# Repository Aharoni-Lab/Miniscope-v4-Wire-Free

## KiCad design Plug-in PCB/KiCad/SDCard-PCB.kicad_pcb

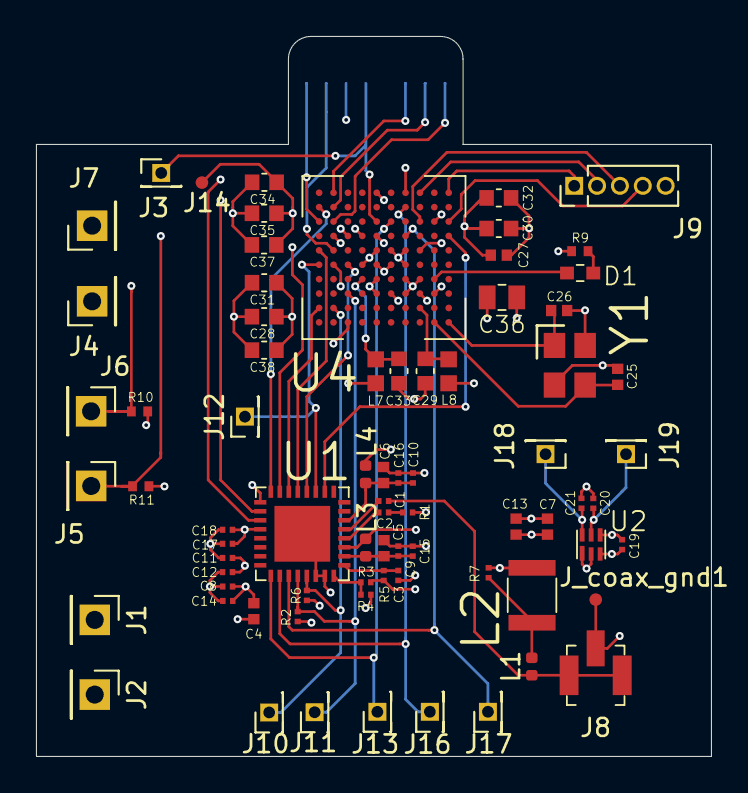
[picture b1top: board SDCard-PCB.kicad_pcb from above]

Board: 4 copper layers, 37.5 x 40.0 mm, 76 parts (1 on the bottom side), 47 nets.

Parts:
C1, C8, C9, C10, C11, C12: GRM033R61A104ME15D; C_0201_0603Metric_L
C2: GRM033R61C473KE84D; C_0201_0603Metric_L
C3, C19, C20, C21: GRM033R61A105ME15D; C_0201_0603Metric_L
C4, C5: GRM155R60J475ME47D; C_0402_1005Metric_L
C6: GRJ155R60J106ME11D; C_0402_1005Metric_L
C7, C13: GRM155R60J106ME15D; C_0402_1005Metric_L
C14, C15, C16, C17, C18: GRM033R71A103KA01D; C_0201_0603Metric_L
C25, C26: GRM1555C1H120JA01D; C_0402_1005Metric_L
C27: GRM155R60J475ME87D; C_0402_1005Metric_L
C28, C29, C30, C31, C32, C33, C34, C35, C37, C38: GCJ188R71E104KA12D; C_0603_1608Metric_L
C36: GCM21BR71E105KA56L; C_0805_2012Metric_L
D1: Vishay / Lite-On LTST-C191KRKT; LED_SC80X160X65L40L
J1, J2, J4, J5, J6, J7: Conn_01x01; PinHeader_1x01_P2.54mm_Vertical
J3, J10, J11, J12, J13, J16, J17, J18, J19: Conn_01x01; PinHeader_1x01_P1.27mm_Vertical
J8: Conn_Coaxial; U_FL-R-SMT_10_
J9: Conn_01x05; PinHeader_1x05_P1.27mm_Vertical
J14: Conn_01x01; Conn_1x1_700_Circular_Pad
J15: Conn_01x08; 1x8_microSD
J_coax_gnd1: Conn_01x01; Conn_1x1_700_Circular_Pad
L1, L3, L4: BLM15HD102SN1D; L_0402_1005Metric
L2: ADL3225V-470MT-TL000; L_1210_3225Metric_L
L7, L8: BLM18PG471SN1D; L_0603_1608Metric_L
R1: ERJ-1GEF49R9C; R_0201_0603Metric_ERJ_L
R2, R6: ERJ-1GEF3321C; R_0201_0603Metric_ERJ_L
R3, R5: ERJ-1GEF1002C; R_0201_0603Metric_ERJ_L
R4: ERJ-1GEF1003C; R_0201_0603Metric_ERJ_L
R7: MMBT3904LP-7B; R_0201_0603Metric_ERJ_L
R9: 499; R_0402_1005Metric_ERJ_L
R10, R11: 100k; R_0402_1005Metric_ERJ_L
U1: DS90UB933-Q1; QFN_33_P50_500X500X80L40X24T310L
U2: TLV7103318DSER; SON_6_P50_150X150X80L50X25L
U4: ATSAME70N21A-CN; BGA_100_CP80_10X10_900X900X110B40L
Y1: ABM8G-12.000MHZ-4Y-T3; OSCCC320X250X100L80X100

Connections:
+1V2: C34.1, C35.1, C36.1, C37.1, J14.1, L7.1, L8.2, U4.C3, U4.C6, U4.D6, U4.G6
+1V8: C4.1, C8.1, C11.1, C12.1, C14.1, C17.1, C18.1, C20.1, C27.1, C28.1, C30.1, C31.1, C32.1, C38.1, J2.1, J4.1, J19.1, L3.2, L4.2, R3.1, R5.1, R10.1, R11.1, U1.11, U1.25, U1.28, U2.5, U4.C2, U4.C5, U4.E5, U4.E6, U4.F3, U4.G7
+3V3: C21.1, J1.1, J18.1, R2.1, R6.1, U2.6
+5V: C7.1, C13.1, C19.1, L2.2, R7.1, U2.1, U2.2, U2.3
/Connectors/SWDCLK-Rec: J6.1, R10.2, U4.E9
/Connectors/SWDIO-Rec: J5.1, R11.2, U4.G8
/OnBoardMCU/FRAME_VALID: J16.1, U1.2, U4.J4
/OnBoardMCU/IMG_out0: J12.1, U1.19, U4.E10
/OnBoardMCU/IMG_out1: U1.20, U4.E8
/OnBoardMCU/IMG_out2: U1.21, U4.F10
/OnBoardMCU/IMG_out3: U1.22, U4.B10
/OnBoardMCU/IMG_out4: U1.23, U4.G9
/OnBoardMCU/IMG_out5: U1.24, U4.J10
/OnBoardMCU/IMG_out6: U1.26, U4.K6
/OnBoardMCU/IMG_out7: U1.27, U4.K4
/OnBoardMCU/LINE_VALID: J13.1, U1.1, U4.H5
/OnBoardMCU/PXL_CLK: J17.1, U1.3, U4.G4
/OnBoardMCU/RED_LED: D1.2, U4.D2
/OnBoardMCU/SCL: J11.1, R2.2, U1.4, U4.C8
/OnBoardMCU/SDA: J10.1, R6.2, U1.5, U4.B9
/OnBoardMCU/SER_CLK: U1.18, U4.G1
/OnBoardMCU/VDDPLL: C33.1, L7.2, U4.D7
/OnBoardMCU/VDDUTMIC: C29.1, L8.1, U4.B3
/OnBoardMCU/WXB_CLK: J3.1, J15.5, U4.H6
/OnBoardMCU/WXB_CMD: J15.3, U4.K9
/OnBoardMCU/WXB_in0: J15.7, U4.F9
/OnBoardMCU/WXB_in1: J15.8, U4.H10
/OnBoardMCU/WXB_in2: J15.1, U4.H9
/OnBoardMCU/WXB_in3: J15.2, U4.J9
/OnBoardMCU/XIN: C26.1, U4.A1, Y1.1
/OnBoardMCU/XOUT: C25.1, U4.A2, Y1.3
/OnBoardMCU/test1: J9.1, U4.K1
/OnBoardMCU/test2: J9.2, U4.K3
/OnBoardMCU/test3: J9.3, U4.H3
/OnBoardMCU/test4: J9.4, U4.H1
/OnBoardMCU/test5: J9.5, U4.H2
/Serializer/DOUT_P: C1.1, J8.1, L1.1
/Serializer/MODE: R3.2, R4.1, U1.8
/Serializer/PDB: C3.1, R5.2, U1.9
/Serializer/VDDCML: C6.1, C10.1, C16.1, L4.1, U1.14
/Serializer/VDDPLL: C5.1, C9.1, C15.1, L3.1, U1.10
Earth: C3.2, C4.2, C5.2, C6.2, C7.2, C8.2, C9.2, C10.2, C11.2, C12.2, C13.2, C14.2, C15.2, C16.2, C17.2, C18.2, C19.2, C20.2, C21.2, C25.2, C26.2, C27.2, C28.2, C29.2, C30.2, C31.2, C32.2, C33.2, C34.2, C35.2, C36.2, C37.2, C38.2, J7.1, J8.2, J15.6, J_coax_gnd1.1, R1.1, R4.2, R9.2, U1.6, U1.7, U1.33, U2.4, U4.A8, U4.C4, U4.D3, U4.D4, U4.E4, U4.E7, U4.F4, U4.F5, U4.F6, Y1.2, Y1.4
unnamed: C1.2, U1.13
unnamed: C2.1, R1.2
unnamed: C2.2, U1.12
unnamed: D1.1, R9.1
unnamed: L1.2, L2.1, R7.2
